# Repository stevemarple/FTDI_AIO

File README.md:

# FTDI all-in-one

The FTDI all-in-one is a USB-UART converter, a bit-banging AVR ISP 
programmer, a breakout board and USB switch and LED.

## License

Unless indicated otherwise hardware is released under the Creative
Commons Attribution-ShareAlike 3.0 Unported (CC BY-SA 3.0)
http://creativecommons.org/licenses/by-sa/3.0/

Unless indicated otherwise software is released under the GNU Lesser
General Public License, version 2.1.
http://www.gnu.org/licenses/lgpl-2.1.html

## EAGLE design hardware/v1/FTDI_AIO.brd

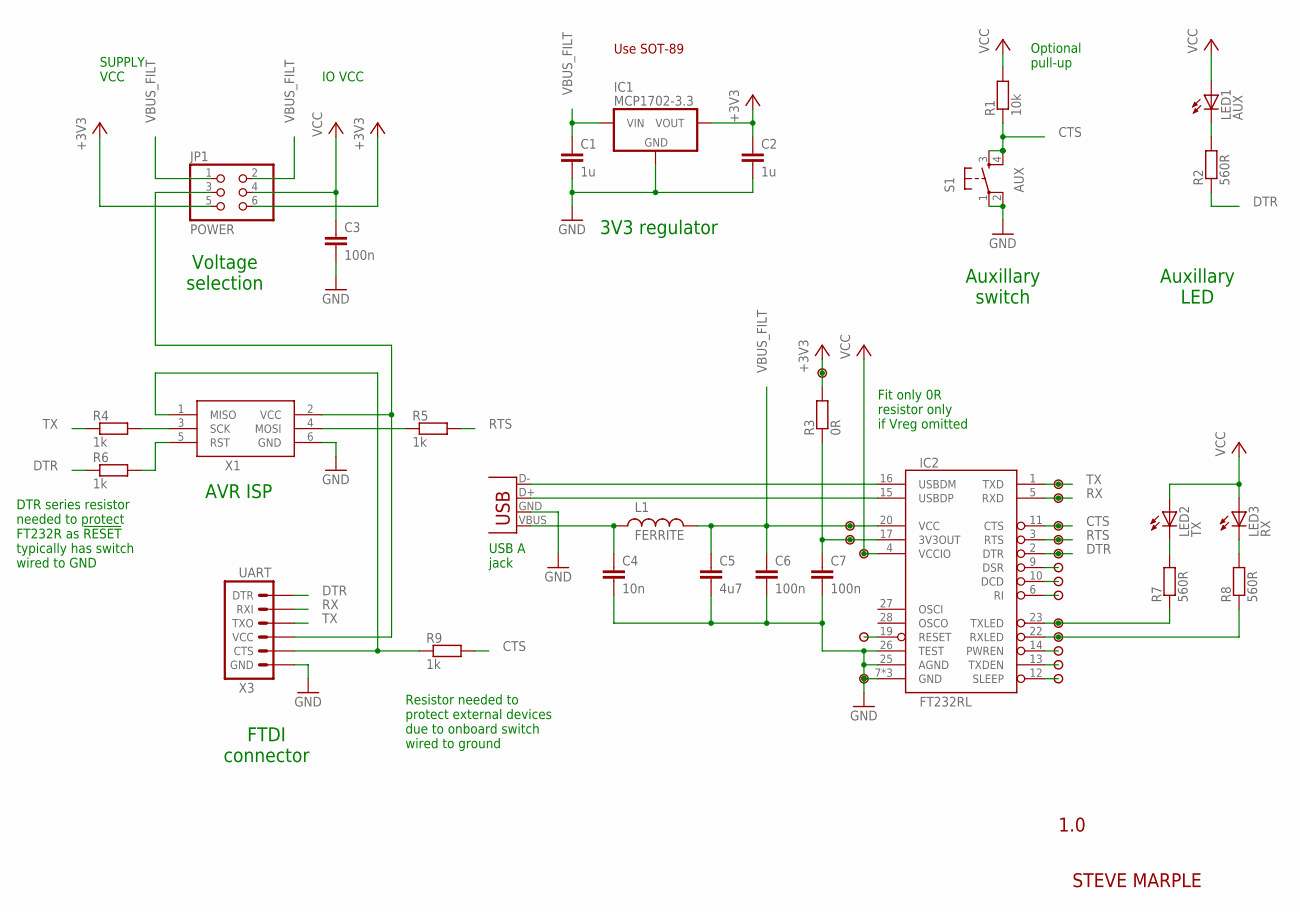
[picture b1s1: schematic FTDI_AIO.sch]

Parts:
C1, C2: 1u; 1206-HAND
C3, C6, C7: 100n; 1206-HAND
C4: 10n; 1206-HAND
C5: 4u7; 1206-HAND
IC1: MCP1702-3.3; TO-92
IC2: FT232RL; SSOP28-HAND
JP1: POWER; 2X03
L1: FERRITE; 0805-HAND
LED1: AUX; LED3MM
LED2: TX; LED3MM
LED3: RX; LED3MM
R1: 10k; 1206-HAND
R2, R7, R8: 560R; 1206-HAND
R3: 0R; 1206-HAND
R4, R5, R6, R9: 1k; 1206-HAND
S1: AUX; TACTILE-PTH
U$1, U$2, U$3, U$4, U$5, U$6, U$7, U$8, U$9, U$10, U$11, U$12, U$13, U$14, U$15, U$16, U$17, U$18, U$19: PAD
X1: ISP; CONN-HARTING-ML6
X2: USB-A-H
X3: UART; 1X06

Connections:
3V3_OUT: C7.1, IC2.17 (3V3OUT), R3.1, U$6.1
!RESET: IC2.19 (RESET), U$14.1
+3V3: C2.1, IC1.3 (VOUT), JP1.5, JP1.6, R3.2, U$1.1
CTS: IC2.11 (CTS), R1.1, R9.2, S1.3, S1.4, U$5.1
CTS_PROT: R9.1, X1.1 (MISO), X3.5 (CTS)
DTR: IC2.2 (DTR), R2.1, R6.1, U$9.1, X3.1 (DTR)
EXT_VCC: JP1.3, X1.2 (VCC), X3.4 (VCC)
GND: C1.2, C2.2, C3.2, C4.2, C5.2, C6.2, C7.2, IC1.1 (GND), IC2.7 (GND), IC2.18 (GND), IC2.21 (GND), IC2.25 (AGND), IC2.26 (TEST), S1.1, S1.2, U$18.1, X1.6 (GND), X2.GND (VBUS), X3.6 (GND)
unnamed: LED1.K (C), R2.2
unnamed: R5.1, X1.4 (MOSI)
unnamed: LED2.K (C), R7.2
unnamed: LED3.K (C), R8.2
unnamed: IC2.9 (DSR), U$10.1
unnamed: IC2.10 (DCD), U$11.1
unnamed: IC2.6 (RI), U$12.1
unnamed: IC2.14 (PWREN), U$16.1
unnamed: IC2.13 (TXDEN), U$17.1
unnamed: IC2.12 (SLEEP), U$19.1
RST: R6.2, X1.5 (RST)
RTS: IC2.3 (RTS), R5.2, U$7.1
RX: IC2.5 (RXD), U$3.1, X3.2 (RXI)
RXLED: IC2.22 (RXLED), R8.1, U$15.1
SCK: R4.2, X1.3 (SCK)
TX: IC2.1 (TXD), R4.1, U$2.1, X3.3 (TXO)
TXLED: IC2.23 (TXLED), R7.1, U$13.1
USB_D+: IC2.15 (USBDP), X2.D+ (D-)
USB_D-: IC2.16 (USBDM), X2.D- (D+)
VBUS_FILT: C1.1, C5.1, C6.1, IC1.2 (VIN), IC2.20 (VCC), JP1.1, JP1.2, L1.2, U$4.1
VCC: C3.1, IC2.4 (VCCIO), JP1.4, LED1.A, LED2.A, LED3.A, R1.2, U$8.1
VUSB: C4.1, L1.1, X2.VBUS (GND)

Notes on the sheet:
FTDI connector
Optional pull-up
IO VCC
SUPPLY VCC
AVR ISP
Voltage selection
Auxillary switch
Auxillary LED
1.0
STEVE MARPLE
USB A jack
3V3 regulator
Use SOT-89
Fit only 0R resistor only if Vreg omitted
Resistor needed to protect external devices due to onboard switch wired to ground
DTR series resistor needed to protect FT232R as !RESET! typically has switch wired to GND

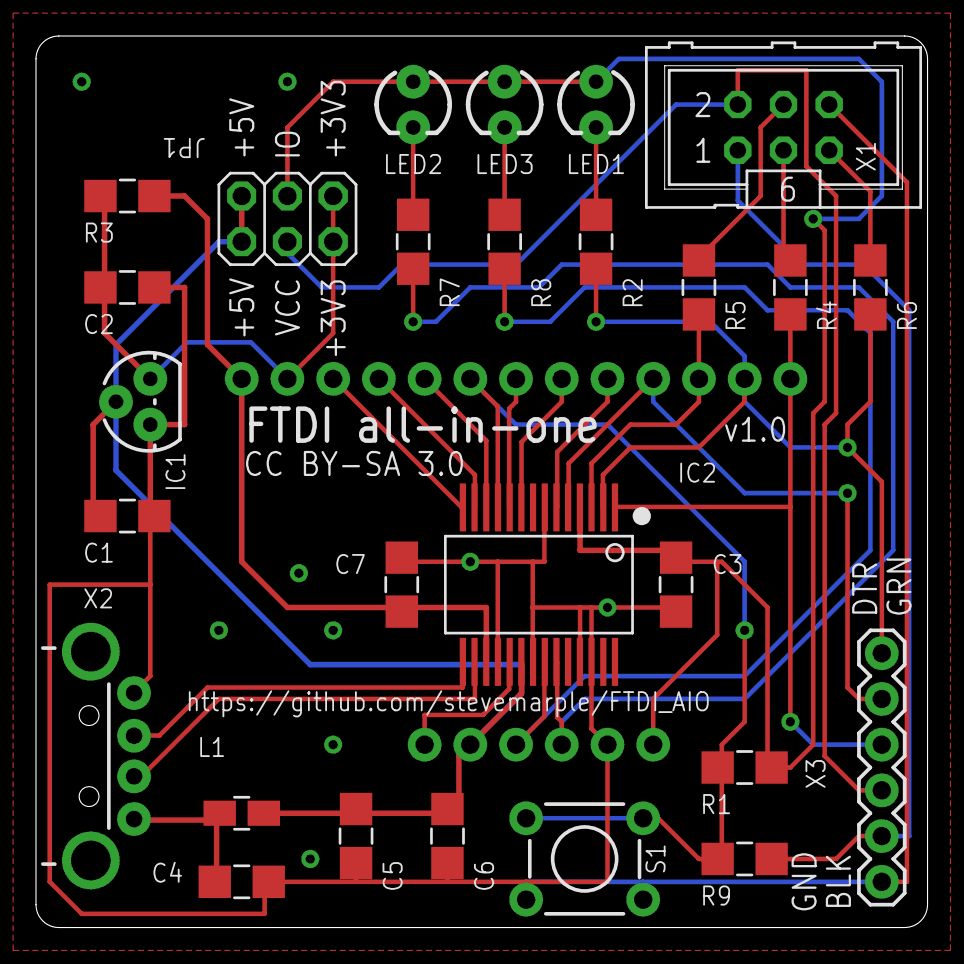
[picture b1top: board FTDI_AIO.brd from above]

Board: 2 copper layers, 49.5 x 49.5 mm, 46 parts (0 on the bottom side), 30 nets.

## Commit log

2014-10-27 Adding README and hardware design files.
2014-10-27 Moved jumper block. Updated FT232RL package.
    Jumper block moved to make room for larger text describing jumper options.
    Updated FT232RL so that silkscreen does not printer over pads.
2014-10-27 Increasing power line track width to 0.012".
2014-10-28 Adding ignore file for Eagle.
2014-10-28 Rounding corners and adding vias between ground planes.
2014-10-28 Minor track and via changes.
2014-10-30 Adding CAM file for Gerber file creation.
2014-10-30 Adding design rules files for 10 mil track and spacing.
2014-11-02 Adding Eagle library.
2014-11-04 Updating to use modified FT232R package. Rerouted TXLED.
    TXLED signal rerouted to avoid breaking ground place in vicinity of
    USB data lines.
2014-11-04 Updating to lastet version of eagle library.
2014-11-04 Swapping capcitor positions for better decoupling.
2014-11-04 Adding decoupling capacitor for FT232R VCCIO.
2014-11-04 Updating library to use a .gitignore for Eagle backup files.
2014-11-04 Adding Gerber files.
2014-11-06 Ensuring all silkscreen is within board outline.
2014-11-24 Adding initial files for manual.
2014-11-24 First draft of manual.
2014-11-25 Adding missing files.
2014-11-25 Adding dummy section for operation.
2014-11-26 Adding schematic and other documentation.
2014-11-26 Adding schematic and PCB layout.
2014-11-27 Adding licence file.
2014-11-27 Including Github repository URL in manual.
2014-11-29 Correcting licence description.

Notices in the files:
hardware/v1/FTDI_AIO.brd:
Copyright Steve Marple 2014
parts and their libraries:
SparkFun: Licensing: CC v3.0 Share-Alike You are welcome to use this library for commercial purposes.
